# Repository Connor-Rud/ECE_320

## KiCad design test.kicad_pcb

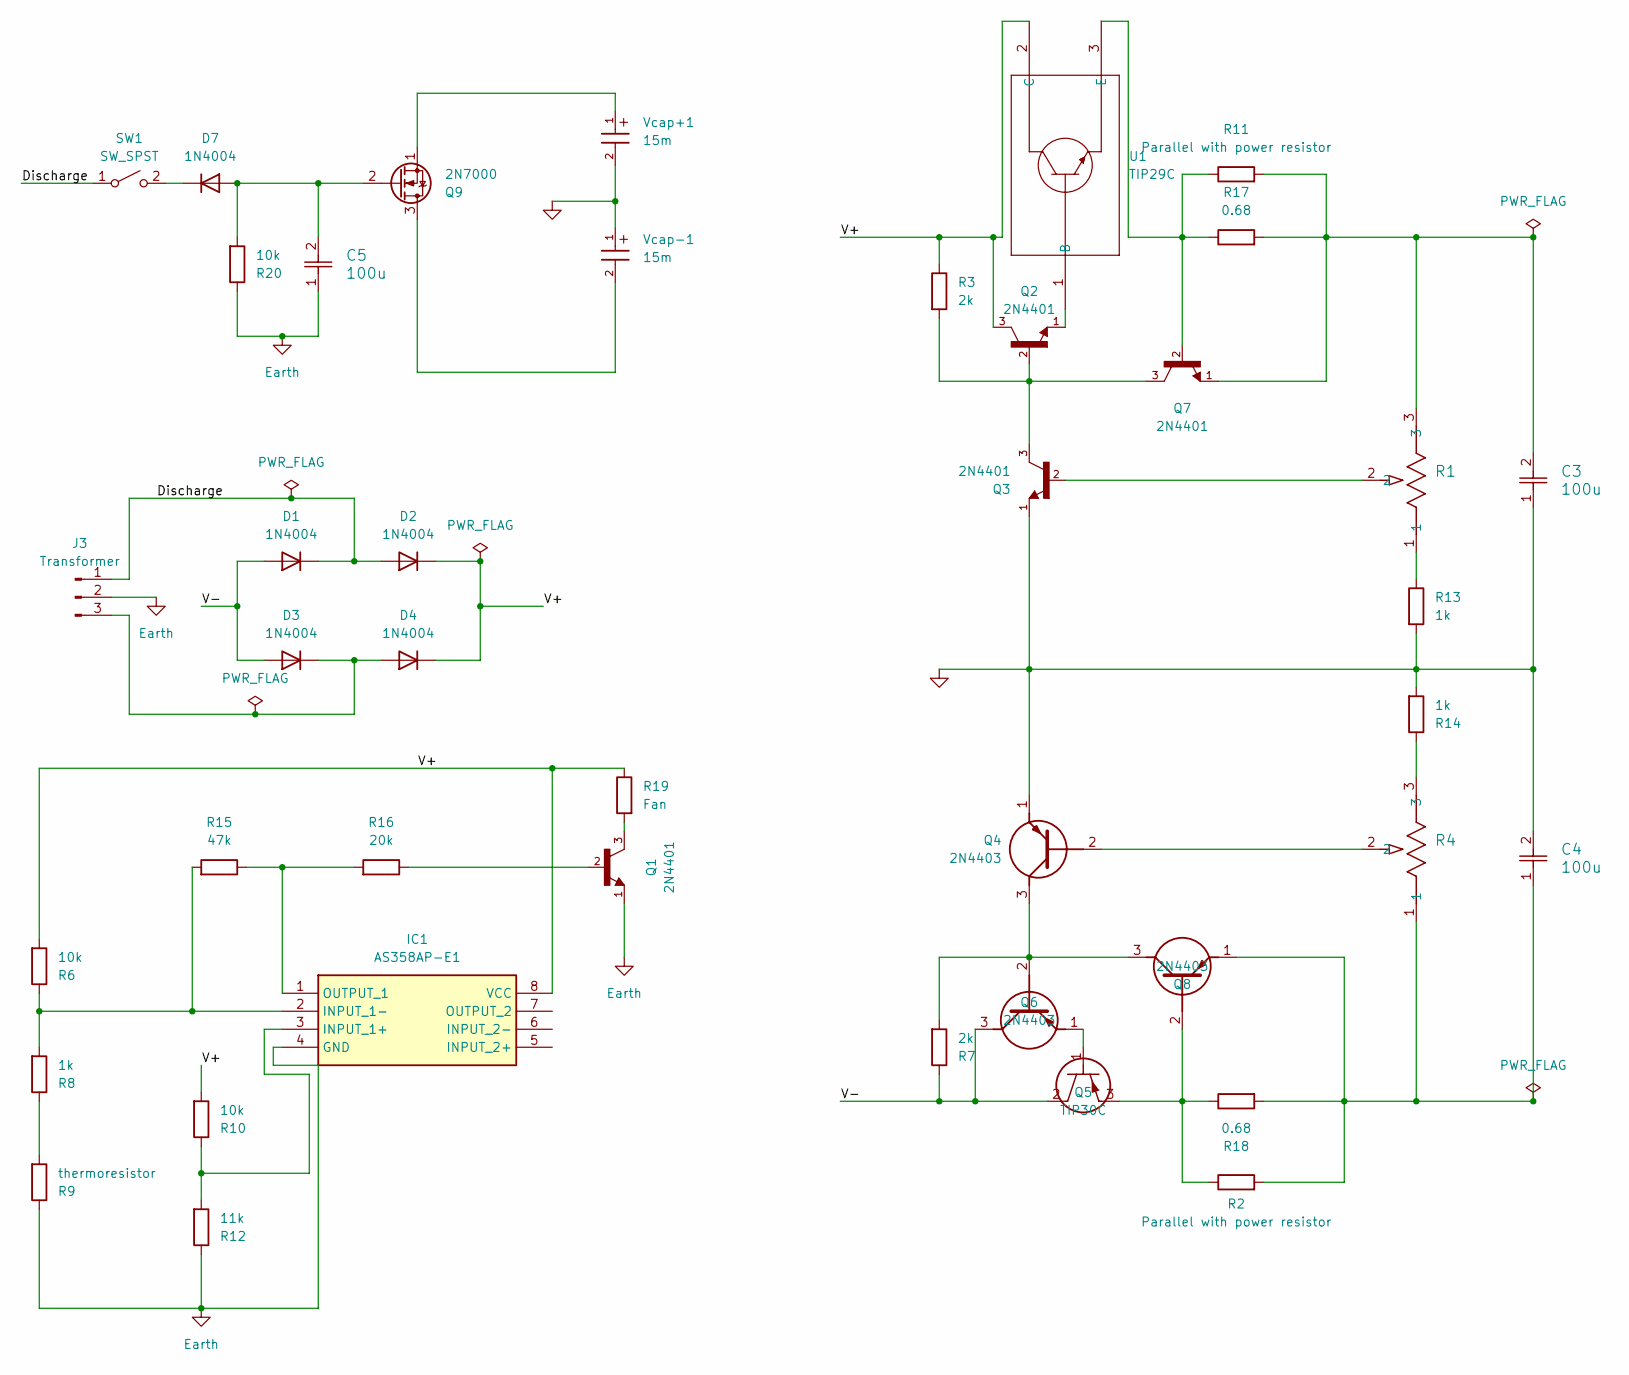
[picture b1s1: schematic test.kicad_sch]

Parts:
C3, C4, C5: 100u; WCAP-ATET_8X11.5_DXL_
D1, D2, D3, D4, D7: 1N4004; D_DO-41_SOD81_P10.16mm_Horizontal
IC1: AS358AP-E1; DIP762W56P254L930H431Q8N; Mouser Part Number 621-AS358AP-E1
J3: Transformer; TerminalBlock_MaiXu_MX126-5.0-03P_1x03_P5.00mm
Q1, Q2, Q3, Q7: 2N4401; TO92
Q4, Q6, Q8: 2N4403; Mouser Part Number 512-2N4403
Q5: TIP30C; TO-220_STM
Q9: 2N7000; TO-92_Inline
R1, R4: P160KN-0QC15B100K; POT_P160KN_TTE
R2, R11: Parallel with power resistor; R_Axial_DIN0207_L6.3mm_D2.5mm_P15.24mm_Horizontal
R3, R7: 2k; R_Axial_DIN0207_L6.3mm_D2.5mm_P15.24mm_Horizontal
R6, R10, R20: 10k; R_Axial_DIN0207_L6.3mm_D2.5mm_P15.24mm_Horizontal
R8, R13, R14: 1k; R_Axial_DIN0207_L6.3mm_D2.5mm_P15.24mm_Horizontal
R9: thermoresistor; R_Axial_DIN0204_L3.6mm_D1.6mm_P5.08mm_Horizontal
R12: 11k; R_Axial_DIN0207_L6.3mm_D2.5mm_P15.24mm_Horizontal
R15: 47k; R_Axial_DIN0207_L6.3mm_D2.5mm_P15.24mm_Horizontal
R16: 20k; R_Axial_DIN0207_L6.3mm_D2.5mm_P15.24mm_Horizontal
R17, R18: 0.68; R_Axial_DIN0207_L6.3mm_D2.5mm_P15.24mm_Horizontal
R19: Fan; R_Axial_DIN0207_L6.3mm_D2.5mm_P15.24mm_Horizontal
SW1: SW_SPST; SolderWire-0.1sqmm_1x02_P3.6mm_D0.4mm_OD1mm
U1: TIP29C; TO-220_STM; Mouser Part Number 512-TIP29C
Vcap+1: 15m; CAP_PAN_30X20_PAN
Vcap-1: 15m; CAP_PAN_30X20_PAN

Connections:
/Discharge: D1.1 (K), D2.2 (A), J3.1, SW1.1 (A)
/V+: D2.1 (K), D4.1 (K), IC1.8 (VCC), Q2.3, R3.1, R6.2, R10.2, R19.1, U1.2 (C); also elsewhere on the board
/V-: D1.2 (A), D3.2 (A), Q5.2, Q6.3 (C), R7.1
Earth: C3.1, C4.2, C5.1, IC1.4 (GND), J3.2, Q1.1, Q3.1, Q4.1 (E), R9.1, R12.1, R13.2, R14.2, R20.1, Vcap+1.2, Vcap-1.1
unnamed: C3.2, Q7.1, R1.3, R11.2, R17.2
unnamed: D3.1 (K), D4.2 (A), J3.3
unnamed: C5.2, D7.2 (A), Q9.2 (G), R20.2
unnamed: D7.1 (K), SW1.2 (B)
unnamed: IC1.3 (INPUT_1+), R10.1, R12.2
unnamed: IC1.2 (INPUT_1-), R6.1, R8.2, R15.2
unnamed: IC1.1 (OUTPUT_1), R15.1, R16.2
unnamed: Q1.2, R16.1
unnamed: Q1.3, R19.2
unnamed: Q2.2, Q3.3, Q7.3, R3.2
unnamed: Q3.2, R1.2
unnamed: Q4.2 (B), R4.2
unnamed: Q4.3 (C), Q6.2 (B), Q8.3 (C), R7.2
unnamed: Q5.1, Q6.1 (E)
unnamed: Q5.3, Q8.2 (B), R2.1, R18.1
unnamed: C4.1, Q8.1 (E), R2.2, R4.1, R18.2
unnamed: Q9.3 (D), Vcap-1.2
unnamed: Q9.1 (S), Vcap+1.1
unnamed: R1.1, R13.1
unnamed: R8.1, R9.2
unnamed: R4.3, R14.1
unnamed: Q2.1, U1.1 (B)
unnamed: Q7.2, R11.1, R17.1, U1.3 (E)

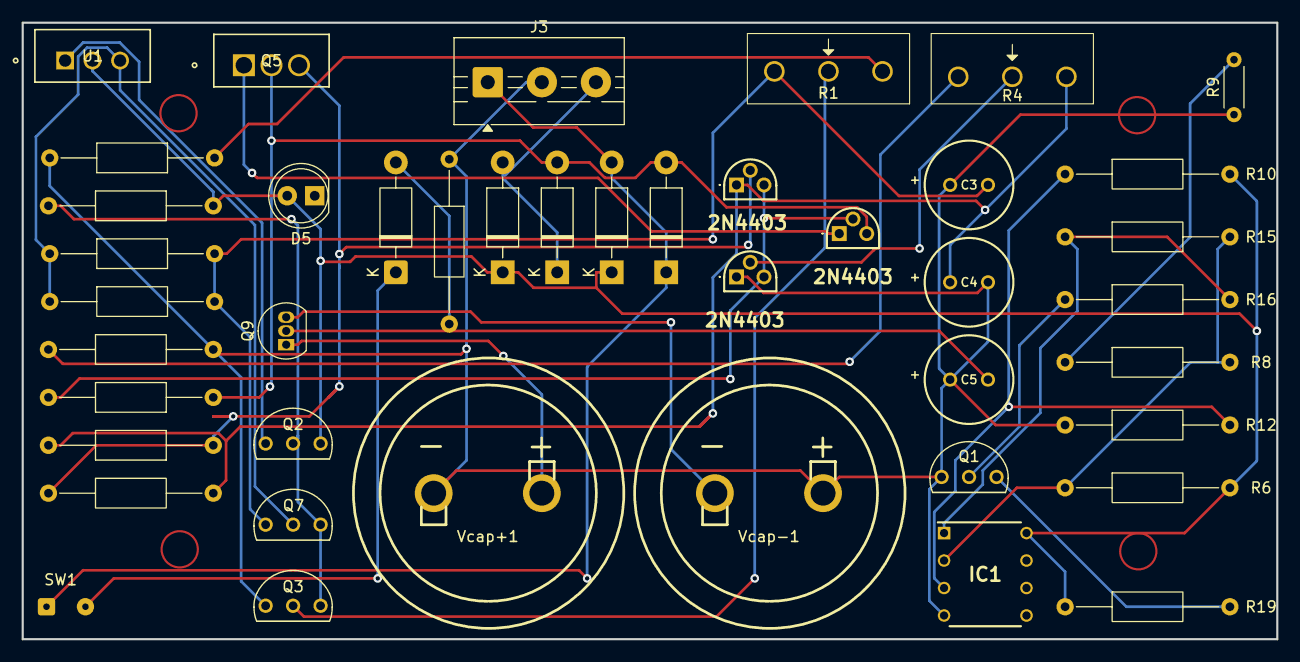
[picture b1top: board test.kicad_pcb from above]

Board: 2 copper layers, 116.0 x 57.0 mm, 43 parts (0 on the bottom side), 27 nets.

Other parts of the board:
D5: LED_I; LED_D5.0mm

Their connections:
/V+: D5.2 (A); also elsewhere on the board

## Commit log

2025-11-17 test
2025-11-17 test done
2025-11-17 changed
2025-11-17 test branch
2025-11-18 Updated by Bryce Tue 11/18/2025 7:59
2025-11-19 Updated by Bryce Wed 11/19/2025 8:55
2025-11-20 Updated by Bryce Thu 11/20/2025 8:01
2025-11-20 Updated by Bryce Thu 11/20/2025 13:12
2025-11-21 Updated by Bryce Thu 11/20/2025 22:02
2025-11-21 Updated by Bryce Thu 11/20/2025 22:43
2025-11-22 Updated by Bryce Sat 11/22/2025 15:42
